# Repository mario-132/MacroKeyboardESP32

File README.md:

# Macro Keyboard
This is a PCB design for a macro keyboard using the ESP32, I'm still writing the software to make proper use of this but the hardware is confirmed working.

It supports both USB and Bluetooth for keyboard input. It supports mechanical switches and has RGB LED's for below the keys. It can be used with a li-ion battery and has a USB port for charging and power.

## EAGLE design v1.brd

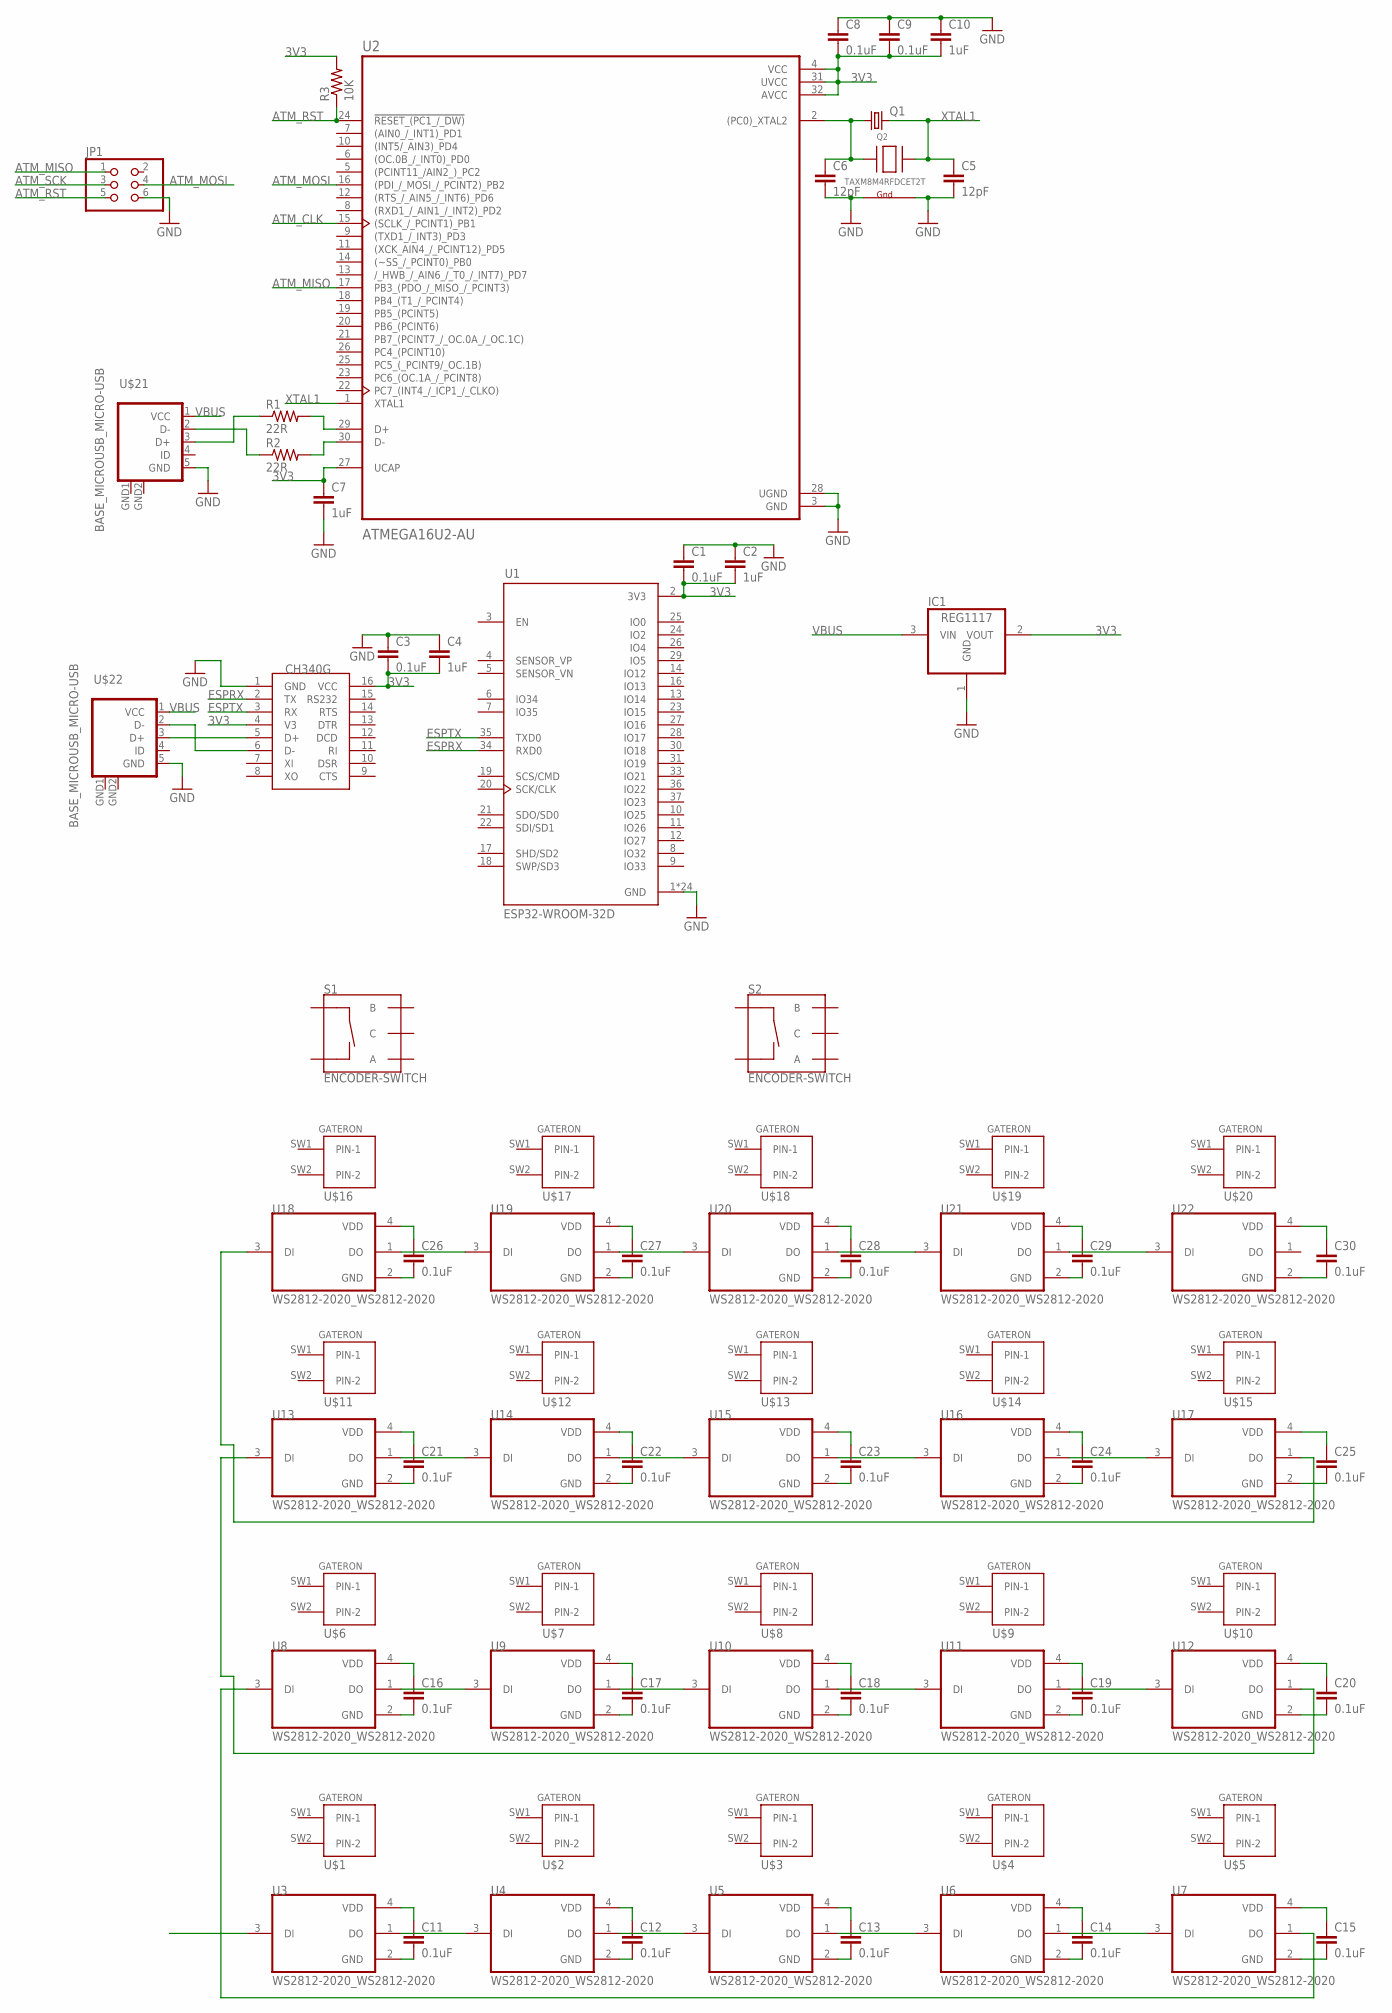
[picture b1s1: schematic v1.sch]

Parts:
C1, C3, C8, C9, C11, C12, C13, C14, C15, C16, C17, C18, C19, C20, C21, C22, C23, C24, C25, C26, C27, C28, C29, C30: 0.1uF; C0805
C2, C4, C7, C10: 1uF; C0805
C5, C6: 12pF; C0805
IC1: REG1117; SOT223
JP1: PINHD-2X3; 2X03
Q1: CRYSTALHC49UP; HC49UP
Q2: TAXM8M4RFDCET2T; NX3225
R1, R2: 22R; R0805
R3: 10K; R0805
S1, S2: ENCODER-SWITCH; ROTARY_ENC_PLAIN
U1: ESP32-WROOM-32D; MODULE_ESP32-WROOM-32D
U2: ATMEGA16U2-AU; QFP80P900X900X120-32N
U3, U4, U5, U6, U7, U8, U9, U10, U11, U12, U13, U14, U15, U16, U17, U18, U19, U20, U21, U22: WS2812-2020_WS2812-2020; WS2812-2020_LED_WS2812-2020
U$1, U$2, U$3, U$4, U$5, U$6, U$7, U$8, U$9, U$10, U$11, U$12, U$13, U$14, U$15, U$16, U$17, U$18, U$19, U$20: GATERON
U$21, U$22: BASE_MICROUSB_MICRO-USB
U$23: CH340G_CH340G; CH340G_SOIC16

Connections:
3V3: C1.2, C2.2, C3.2, C4.2, C7.1, C8.2, C9.2, C10.2, IC1.2 (VOUT), R3.2, U1.2 (3V3), U2.4 (VCC), U2.27 (UCAP), U2.31 (UVCC), U2.32 (AVCC), U$23.4 (V3), U$23.16 (VCC)
ATM_CLK: U2.15 ((SCLK_/_PCINT1)_PB1)
ATM_MISO: JP1.1, U2.17 (PB3_(PDO_/_MISO_/_PCINT3))
ATM_MOSI: JP1.4, U2.16 ((PDI_/_MOSI_/_PCINT2)_PB2)
ATM_RST: JP1.5, R3.1, U2.24 (!RESET_(PC1_/_DW))
ATM_SCK: JP1.3
ESPRX: U1.34 (RXD0), U$23.2 (TX)
ESPTX: U1.35 (TXD0), U$23.3 (RX)
GND: C1.1, C2.1, C3.1, C4.1, C5.2, C6.2, C7.2, C8.1, C9.1, C10.1, IC1.1 (GND), JP1.6, Q2.2 (G2), Q2.4 (G1), U1.1 (GND), U1.15 (GND), U1.38 (GND), U1.39_1 (GND), U1.39_2 (GND), U1.39_3 (GND), U1.39_4 (GND), U1.39_5 (GND), U1.39_6 (GND), U1.39_7 (GND), U1.39_8 (GND), U1.39_9 (GND), U1.39_10 (GND), U1.39_11 (GND), U1.39_12 (GND), U1.39_13 (GND), U1.39_14 (GND), U1.39_15 (GND), U1.39_16 (GND), U1.39_17 (GND), U1.39_18 (GND), U1.39_19 (GND), U1.39_20 (GND), U1.39_21 (GND), U2.3 (GND), U2.28 (UGND), U$21.5 (GND), U$21.GND1 (GND), U$21.GND2 (GND), U$22.5 (GND), U$22.GND1 (GND), U$22.GND2 (GND), U$23.1 (GND)
unnamed: R1.1, U$21.3 (D+)
unnamed: R1.2, U2.29 (D+)
unnamed: R2.2, U2.30 (D-)
unnamed: U$22.2 (D-), U$23.6 (D-)
unnamed: R2.1, U$21.2 (D-)
unnamed: U$22.3 (D+), U$23.5 (D+)
unnamed: C6.1, Q1.1, Q2.1 (X1), U2.2 ((PC0)_XTAL2)
unnamed: U3.1 (DO), U4.3 (DI)
unnamed: U4.1 (DO), U5.3 (DI)
unnamed: U5.1 (DO), U6.3 (DI)
unnamed: U6.1 (DO), U7.3 (DI)
unnamed: U7.1 (DO), U8.3 (DI)
unnamed: U8.1 (DO), U9.3 (DI)
unnamed: U9.1 (DO), U10.3 (DI)
unnamed: U10.1 (DO), U11.3 (DI)
unnamed: U11.1 (DO), U12.3 (DI)
unnamed: U12.1 (DO), U13.3 (DI)
unnamed: U13.1 (DO), U14.3 (DI)
unnamed: U14.1 (DO), U15.3 (DI)
unnamed: U15.1 (DO), U16.3 (DI)
unnamed: U16.1 (DO), U17.3 (DI)
unnamed: U17.1 (DO), U18.3 (DI)
unnamed: U18.1 (DO), U19.3 (DI)
unnamed: U19.1 (DO), U20.3 (DI)
unnamed: U20.1 (DO), U21.3 (DI)
unnamed: U21.1 (DO), U22.3 (DI)
unnamed: C11.2, U3.2 (GND)
unnamed: C11.1, U3.4 (VDD)
unnamed: C12.1, U4.4 (VDD)
unnamed: C12.2, U4.2 (GND)
unnamed: C13.2, U5.2 (GND)
unnamed: C13.1, U5.4 (VDD)
unnamed: C14.1, U6.4 (VDD)
unnamed: C14.2, U6.2 (GND)
unnamed: C15.1, U7.4 (VDD)
unnamed: C15.2, U7.2 (GND)
unnamed: C20.1, U12.4 (VDD)
unnamed: C20.2, U12.2 (GND)
unnamed: C19.1, U11.4 (VDD)
unnamed: C19.2, U11.2 (GND)
unnamed: C18.1, U10.4 (VDD)
unnamed: C18.2, U10.2 (GND)
unnamed: C17.1, U9.4 (VDD)
unnamed: C17.2, U9.2 (GND)
unnamed: C16.1, U8.4 (VDD)
unnamed: C16.2, U8.2 (GND)
unnamed: C21.1, U13.4 (VDD)
unnamed: C21.2, U13.2 (GND)
unnamed: C22.1, U14.4 (VDD)
unnamed: C22.2, U14.2 (GND)
unnamed: C23.1, U15.4 (VDD)
unnamed: C23.2, U15.2 (GND)
unnamed: C24.1, U16.4 (VDD)
unnamed: C24.2, U16.2 (GND)
unnamed: C25.1, U17.4 (VDD)
unnamed: C25.2, U17.2 (GND)
unnamed: C30.1, U22.4 (VDD)
unnamed: C30.2, U22.2 (GND)
unnamed: C29.1, U21.4 (VDD)
unnamed: C29.2, U21.2 (GND)
unnamed: C28.1, U20.4 (VDD)
unnamed: C28.2, U20.2 (GND)
unnamed: C27.1, U19.4 (VDD)
unnamed: C27.2, U19.2 (GND)
unnamed: C26.1, U18.4 (VDD)
unnamed: C26.2, U18.2 (GND)
VBUS: IC1.3 (VIN), U$21.1 (VCC), U$22.1 (VCC)
XTAL1: C5.1, Q1.2, Q2.3 (X2), U2.1 (XTAL1)

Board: 2 copper layers, 84 parts (11 on the bottom side), 75 nets, no tracks yet.

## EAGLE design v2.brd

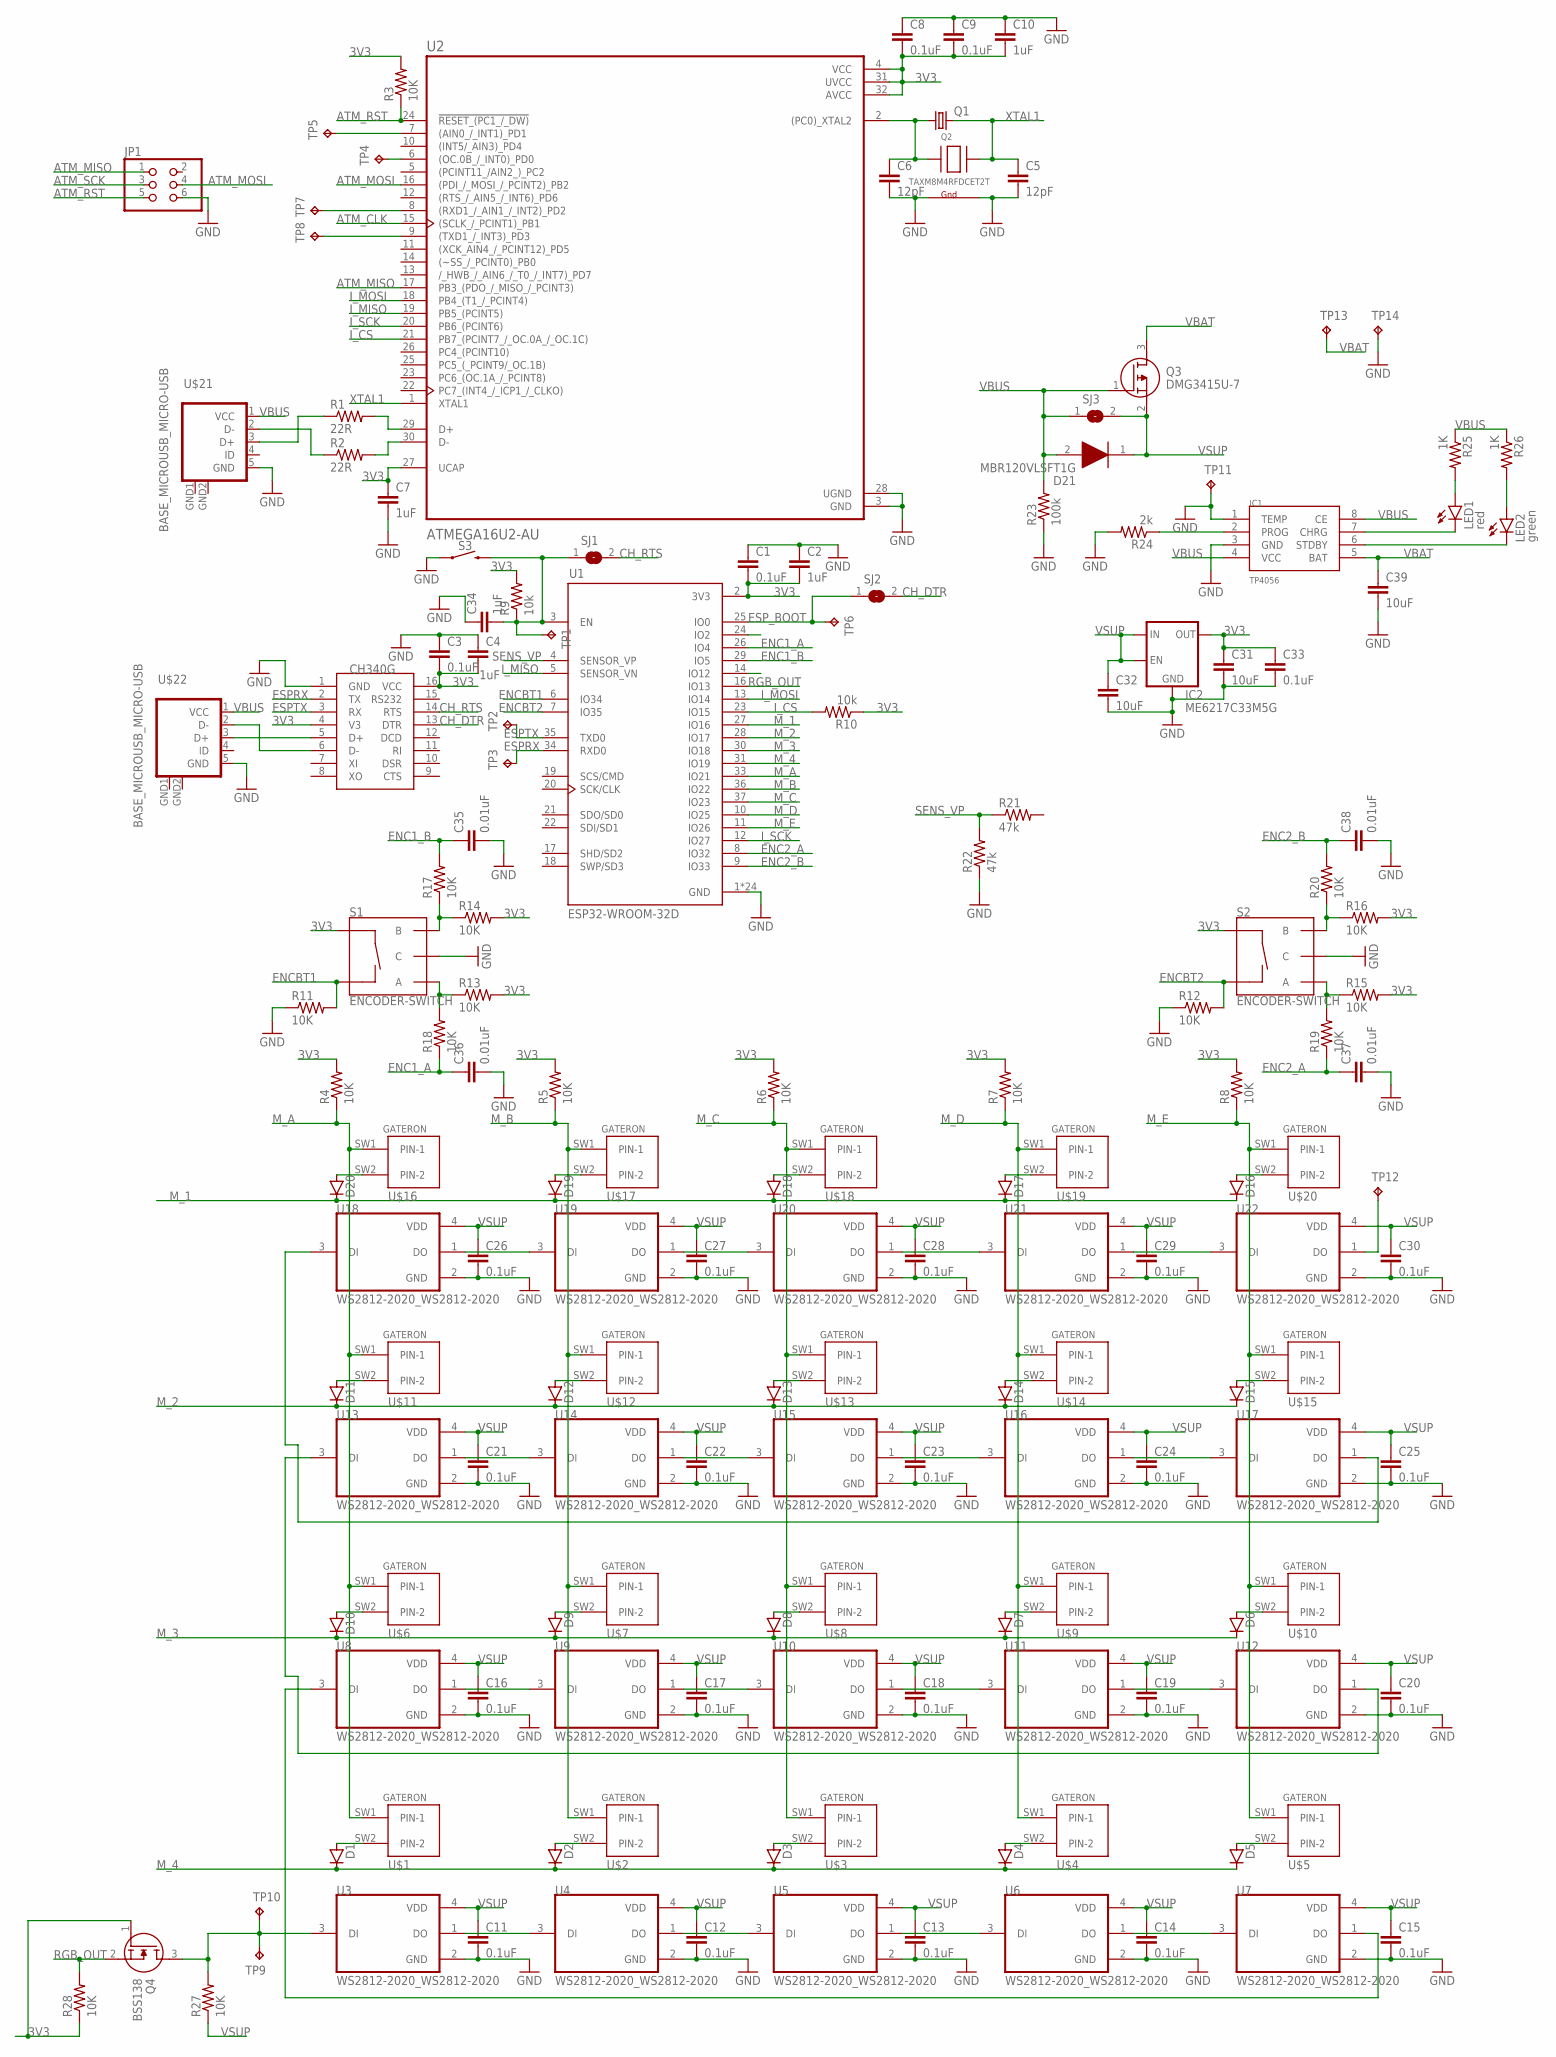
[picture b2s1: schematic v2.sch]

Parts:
C1, C3, C8, C9, C11, C12, C13, C14, C15, C16, C17, C18, C19, C20, C21, C22, C23, C24, C25, C26, C27, C28, C29, C30, C33: 0.1uF; C0805
C2, C4, C7, C10, C34: 1uF; C0805
C5, C6: 12pF; C0805
C31, C32, C39: 10uF; C0805
C35, C36, C37, C38: 0.01uF; C0805
D1, D2, D3, D4, D5, D6, D7, D8, D9, D10, D11, D12, D13, D14, D15, D16, D17, D18, D19, D20: D-SOD123; SOD123
D21: MBR120VLSFT1G; SODFL3616X98N
IC1: TP4056; SOP-8
IC2: ME6217C33M5G; SOT23-5
JP1: PINHD-2X3; 2X03
LED1: red; CHIP-LED0805
LED2: green; CHIP-LED0805
Q1: CRYSTALHC49UP; HC49UP
Q2: TAXM8M4RFDCET2T; NX3225
Q3: DMG3415U-7; SOT96P240X120-3N
Q4: BSS138; SOT95P240X120-3N
R1, R2: 22R; R0805
R3, R4, R5, R6, R7, R8, R11, R12, R13, R14, R15, R16, R17, R18, R19, R20, R27, R28: 10K; R0805
R9, R10: 10k; R0805
R21, R22: 47k; R0805
R23: 100k; R0805
R24: 2k; R0805
R25, R26: 1K; R0805
S1, S2: ENCODER-SWITCH; ROTARY_ENC_PLAIN
S3: MOMENTARY-SWITCH-SPST-SMD-6.0X3.5MM; TACTILE_SWITCH_SMD_6.0X3.5MM
SJ1, SJ2, SJ3: SJ
TP1, TP2, TP3, TP4, TP5, TP6, TP7, TP8, TP9, TP10, TP11, TP12, TP13, TP14: TPTP19R; TP19R
U1: ESP32-WROOM-32D; MODULE_ESP32-WROOM-32D
U2: ATMEGA16U2-AU; QFP80P900X900X120-32N
U3, U4, U5, U6, U7, U8, U9, U10, U11, U12, U13, U14, U15, U16, U17, U18, U19, U20, U21, U22: WS2812-2020_WS2812-2020; WS2812-2020_LED_WS2812-2020
U$1, U$2, U$3, U$4, U$5, U$6, U$7, U$8, U$9, U$10, U$11, U$12, U$13, U$14, U$15, U$16, U$17, U$18, U$19, U$20: GATERON
U$21, U$22: BASE_MICROUSB_MICRO-USB
U$23: CH340G_CH340G; CH340G_SOIC16

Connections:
3V3: C1.2, C2.2, C3.2, C4.2, C7.1, C8.2, C9.2, C10.2, C31.1, C33.1, IC2.5 (OUT), Q4.1 (G), R3.2, R4.2, R5.2, R6.2, R7.2, R8.2, R9.2, R10.1, R13.2, R14.2, R15.2, R16.2, R28.1, S1.SW+, S2.SW+, U1.2 (3V3), U2.4 (VCC), U2.27 (UCAP), U2.31 (UVCC), U2.32 (AVCC), U$23.4 (V3), U$23.16 (VCC)
ATM_CLK: U2.15 ((SCLK_/_PCINT1)_PB1)
ATM_MISO: JP1.1, U2.17 (PB3_(PDO_/_MISO_/_PCINT3))
ATM_MOSI: JP1.4, U2.16 ((PDI_/_MOSI_/_PCINT2)_PB2)
ATM_RST: JP1.5, R3.1, U2.24 (!RESET_(PC1_/_DW))
ATM_SCK: JP1.3
CH_DTR: SJ2.2, U$23.13 (DTR)
CH_RTS: SJ1.2, U$23.14 (RTS)
ENC1_A: C36.1, R18.1, U1.26 (IO4)
ENC1_B: C35.1, R17.2, U1.29 (IO5)
ENC2_A: C37.1, R19.1, U1.8 (IO32)
ENC2_B: C38.1, R20.2, U1.9 (IO33)
ENCBT1: R11.2, S1.SW-, U1.6 (IO34)
ENCBT2: R12.2, S2.SW-, U1.7 (IO35)
ESPRX: TP3.TP, U1.34 (RXD0), U$23.2 (TX)
ESPTX: TP2.TP, U1.35 (TXD0), U$23.3 (RX)
ESP_BOOT: SJ2.1, TP6.TP, U1.25 (IO0)
GND: C1.1, C2.1, C3.1, C4.1, C5.2, C6.2, C7.2, C8.1, C9.1, C10.1, C11.2, C12.2, C13.2, C14.2, C15.2, C16.2, C17.2, C18.2, C19.2, C20.2, C21.2, C22.2, C23.2, C24.2, C25.2, C26.2, C27.2, C28.2, C29.2, C30.2, C31.2, C32.2, C33.2, C34.1, C35.2, C36.2, C37.2, C38.2, C39.2, IC1.1 (TEMP), IC1.3 (GND), IC2.2 (GND), JP1.6, Q2.2 (G2), Q2.4 (G1), R11.1, R12.1, R22.1, R23.1, R24.2, S1.C, S2.C, S3.1, TP11.TP, TP14.TP, U1.1 (GND), U1.15 (GND), U1.38 (GND), U1.39_1 (GND), U1.39_2 (GND), U1.39_3 (GND), U1.39_4 (GND), U1.39_5 (GND), U1.39_6 (GND), U1.39_7 (GND), U1.39_8 (GND), U1.39_9 (GND), U1.39_10 (GND), U1.39_11 (GND), U1.39_12 (GND), U1.39_13 (GND), U1.39_14 (GND), U1.39_15 (GND), U1.39_16 (GND), U1.39_17 (GND), U1.39_18 (GND), U1.39_19 (GND), U1.39_20 (GND), U1.39_21 (GND), U2.3 (GND), U2.28 (UGND), U3.2 (GND), U4.2 (GND), U5.2 (GND), U6.2 (GND), U7.2 (GND), U8.2 (GND), U9.2 (GND), U10.2 (GND), U11.2 (GND), U12.2 (GND), U13.2 (GND), U14.2 (GND), U15.2 (GND), U16.2 (GND), U17.2 (GND), U18.2 (GND), U19.2 (GND), U20.2 (GND), U21.2 (GND), U22.2 (GND), U$21.5 (GND), U$21.GND1 (GND), U$21.GND2 (GND), U$22.5 (GND), U$22.GND1 (GND), U$22.GND2 (GND), U$23.1 (GND)
I_CS: R10.2, U1.23 (IO15), U2.21 (PB7_(PCINT7_/_OC.0A_/_OC.1C))
I_MISO: U1.5 (SENSOR_VN), U2.19 (PB5_(PCINT5))
I_MOSI: U1.13 (IO14), U2.18 (PB4_(T1_/_PCINT4))
I_SCK: U1.12 (IO27), U2.20 (PB6_(PCINT6))
M_1: D16.1 (C), D17.1 (C), D18.1 (C), D19.1 (C), D20.1 (C), U1.27 (IO16)
M_2: D11.1 (C), D12.1 (C), D13.1 (C), D14.1 (C), D15.1 (C), U1.28 (IO17)
M_3: D6.1 (C), D7.1 (C), D8.1 (C), D9.1 (C), D10.1 (C), U1.30 (IO18)
M_4: D1.1 (C), D2.1 (C), D3.1 (C), D4.1 (C), D5.1 (C), U1.31 (IO19)
M_A: R4.1, U1.33 (IO21), U$1.SW1 (PIN-1), U$6.SW1 (PIN-1), U$11.SW1 (PIN-1), U$16.SW1 (PIN-1)
M_B: R5.1, U1.36 (IO22), U$2.SW1 (PIN-1), U$7.SW1 (PIN-1), U$12.SW1 (PIN-1), U$17.SW1 (PIN-1)
M_C: R6.1, U1.37 (IO23), U$3.SW1 (PIN-1), U$8.SW1 (PIN-1), U$13.SW1 (PIN-1), U$18.SW1 (PIN-1)
M_D: R7.1, U1.10 (IO25), U$4.SW1 (PIN-1), U$9.SW1 (PIN-1), U$14.SW1 (PIN-1), U$19.SW1 (PIN-1)
M_E: R8.1, U1.11 (IO26), U$5.SW1 (PIN-1), U$10.SW1 (PIN-1), U$15.SW1 (PIN-1), U$20.SW1 (PIN-1)
unnamed: R1.1, U$21.3 (D+)
unnamed: R1.2, U2.29 (D+)
unnamed: R2.2, U2.30 (D-)
unnamed: U$22.2 (D-), U$23.6 (D-)
unnamed: R2.1, U$21.2 (D-)
unnamed: U$22.3 (D+), U$23.5 (D+)
unnamed: C6.1, Q1.1, Q2.1 (X1), U2.2 ((PC0)_XTAL2)
unnamed: U3.1 (DO), U4.3 (DI)
unnamed: U4.1 (DO), U5.3 (DI)
unnamed: U5.1 (DO), U6.3 (DI)
unnamed: U6.1 (DO), U7.3 (DI)
unnamed: U7.1 (DO), U8.3 (DI)
unnamed: U8.1 (DO), U9.3 (DI)
unnamed: U9.1 (DO), U10.3 (DI)
unnamed: U10.1 (DO), U11.3 (DI)
unnamed: U11.1 (DO), U12.3 (DI)
unnamed: U12.1 (DO), U13.3 (DI)
unnamed: U13.1 (DO), U14.3 (DI)
unnamed: U14.1 (DO), U15.3 (DI)
unnamed: U15.1 (DO), U16.3 (DI)
unnamed: U16.1 (DO), U17.3 (DI)
unnamed: U17.1 (DO), U18.3 (DI)
unnamed: U18.1 (DO), U19.3 (DI)
unnamed: U19.1 (DO), U20.3 (DI)
unnamed: U20.1 (DO), U21.3 (DI)
unnamed: U21.1 (DO), U22.3 (DI)
unnamed: Q4.3 (D), R27.2, TP9.TP, TP10.TP, U3.3 (DI)
unnamed: IC1.2 (PROG), R24.1
unnamed: IC1.7 (CHRG), LED1.C
unnamed: LED1.A, R25.2
unnamed: IC1.6 (STDBY), LED2.C
unnamed: LED2.A, R26.2
unnamed: TP12.TP, U22.1 (DO)
unnamed: R16.1, R20.1, S2.B
unnamed: R15.1, R19.2, S2.A
unnamed: R14.1, R17.1, S1.B
unnamed: R13.1, R18.2, S1.A
unnamed: D1.2 (A), U$1.SW2 (PIN-2)
unnamed: D2.2 (A), U$2.SW2 (PIN-2)
unnamed: D3.2 (A), U$3.SW2 (PIN-2)
unnamed: D4.2 (A), U$4.SW2 (PIN-2)
unnamed: D5.2 (A), U$5.SW2 (PIN-2)
unnamed: D6.2 (A), U$10.SW2 (PIN-2)
unnamed: D15.2 (A), U$15.SW2 (PIN-2)
unnamed: D7.2 (A), U$9.SW2 (PIN-2)
unnamed: D8.2 (A), U$8.SW2 (PIN-2)
unnamed: D13.2 (A), U$13.SW2 (PIN-2)
unnamed: D14.2 (A), U$14.SW2 (PIN-2)
unnamed: D9.2 (A), U$7.SW2 (PIN-2)
unnamed: D10.2 (A), U$6.SW2 (PIN-2)
unnamed: D11.2 (A), U$11.SW2 (PIN-2)
unnamed: D12.2 (A), U$12.SW2 (PIN-2)
unnamed: D20.2 (A), U$16.SW2 (PIN-2)
unnamed: D19.2 (A), U$17.SW2 (PIN-2)
unnamed: D18.2 (A), U$18.SW2 (PIN-2)
unnamed: D17.2 (A), U$19.SW2 (PIN-2)
unnamed: D16.2 (A), U$20.SW2 (PIN-2)
unnamed: C34.2, R9.1, S3.2, SJ1.1, TP1.TP, U1.3 (EN)
unnamed: TP4.TP, U2.6 ((OC.0B_/_INT0)_PD0)
unnamed: TP5.TP, U2.7 ((AIN0_/_INT1)_PD1)
unnamed: TP8.TP, U2.9 ((TXD1_/_INT3)_PD3)
unnamed: TP7.TP, U2.8 ((RXD1_/_AIN1_/_INT2)_PD2)
RGB_OUT: Q4.2 (S), R28.2, U1.16 (IO13)
SENS_VP: R21.1, R22.2, U1.4 (SENSOR_VP)
VBAT: C39.1, IC1.5 (BAT), Q3.3 (D), TP13.TP
VBUS: D21.2 (A), IC1.4 (VCC), IC1.8 (CE), Q3.1 (G), R23.2, R25.1, R26.1, SJ3.1, U$21.1 (VCC), U$22.1 (VCC)
VSUP: C11.1, C12.1, C13.1, C14.1, C15.1, C16.1, C17.1, C18.1, C19.1, C20.1, C21.1, C22.1, C23.1, C24.1, C25.1, C26.1, C27.1, C28.1, C29.1, C30.1, C32.1, D21.1 (K), IC2.1 (IN), IC2.3 (EN), Q3.2 (S), R27.1, SJ3.2, U3.4 (VDD), U4.4 (VDD), U5.4 (VDD), U6.4 (VDD), U7.4 (VDD), U8.4 (VDD), U9.4 (VDD), U10.4 (VDD), U11.4 (VDD), U12.4 (VDD), U13.4 (VDD), U14.4 (VDD), U15.4 (VDD), U16.4 (VDD), U17.4 (VDD), U18.4 (VDD), U19.4 (VDD), U20.4 (VDD), U21.4 (VDD), U22.4 (VDD)
XTAL1: C5.1, Q1.2, Q2.3 (X2), U2.1 (XTAL1)

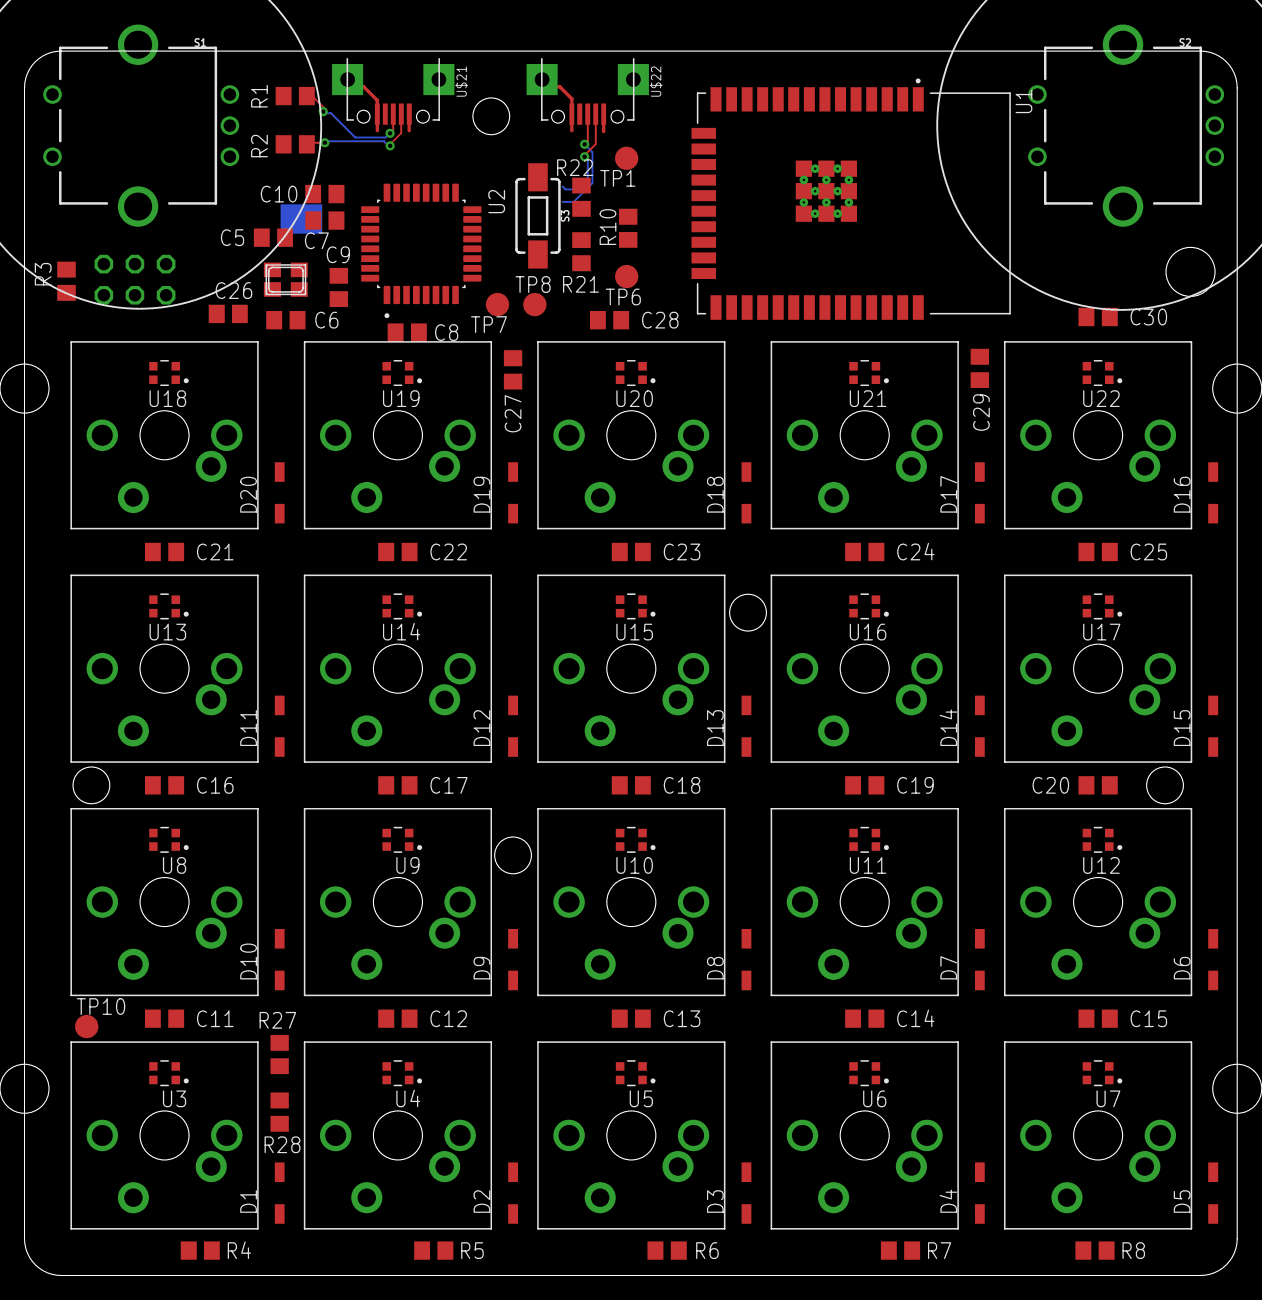
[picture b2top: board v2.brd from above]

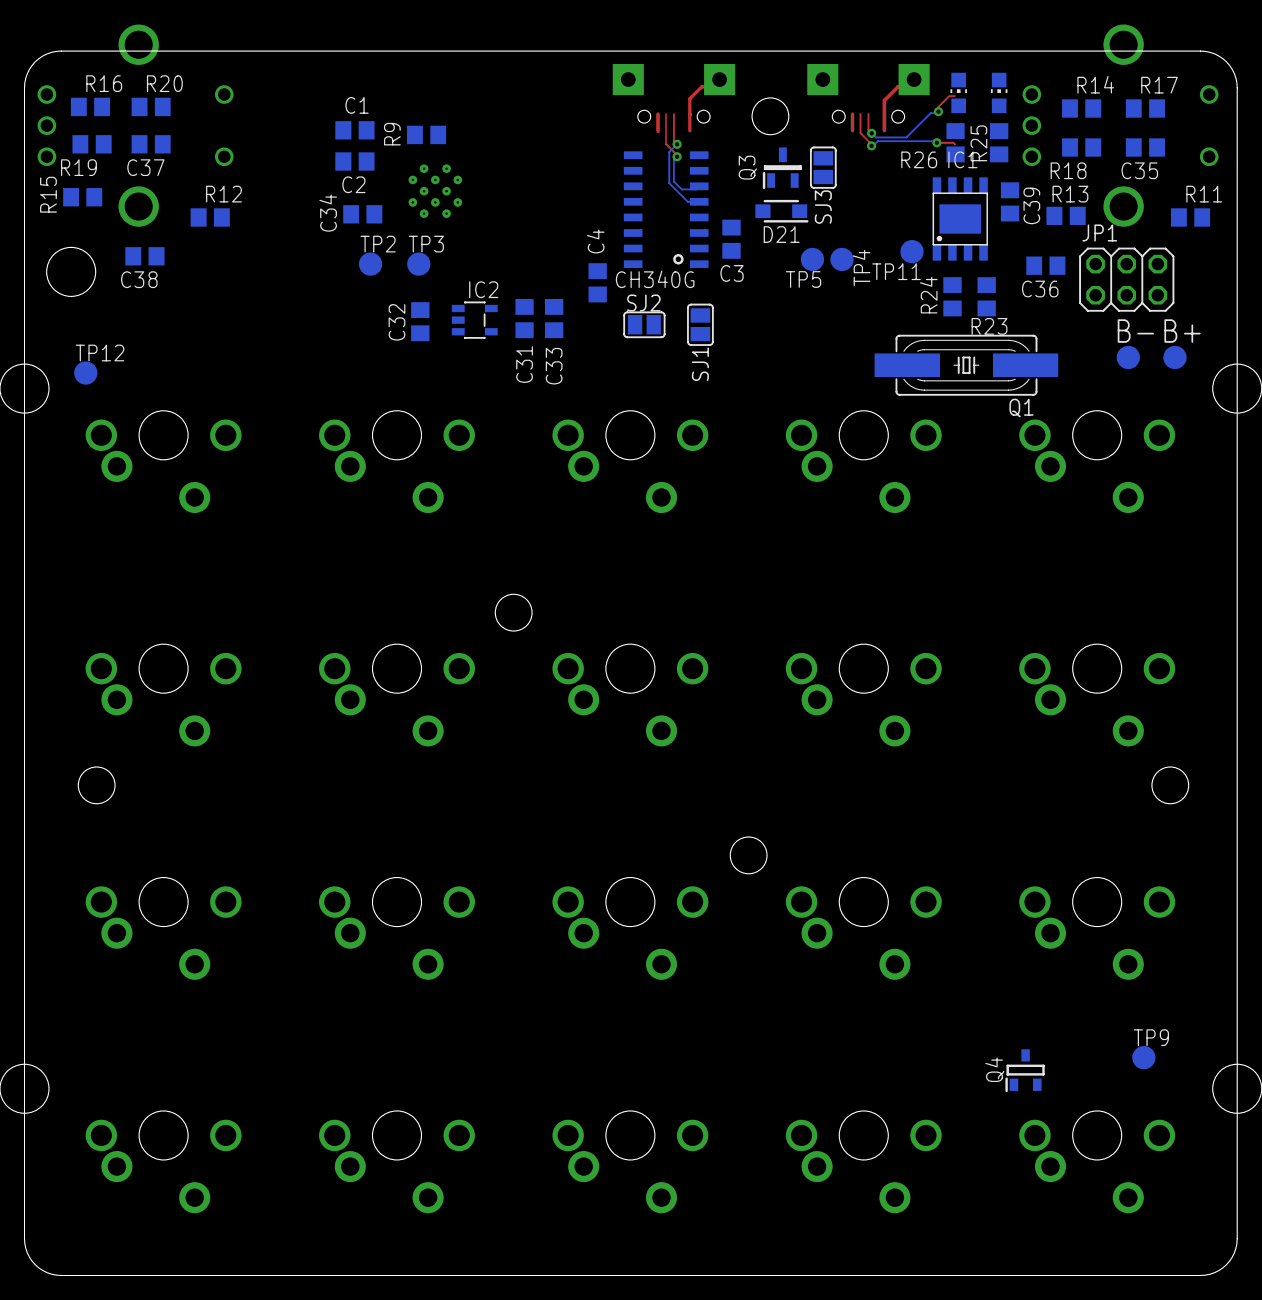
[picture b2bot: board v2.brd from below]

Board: 2 copper layers, 99.0 x 99.9 mm, 162 parts (50 on the bottom side), 97 nets.

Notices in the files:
parts and their libraries:
SparkFun-Switches: Licensing: Creative Commons ShareAlike 4.0 International - https://creativecommons.org/licenses/by-sa/4.0
